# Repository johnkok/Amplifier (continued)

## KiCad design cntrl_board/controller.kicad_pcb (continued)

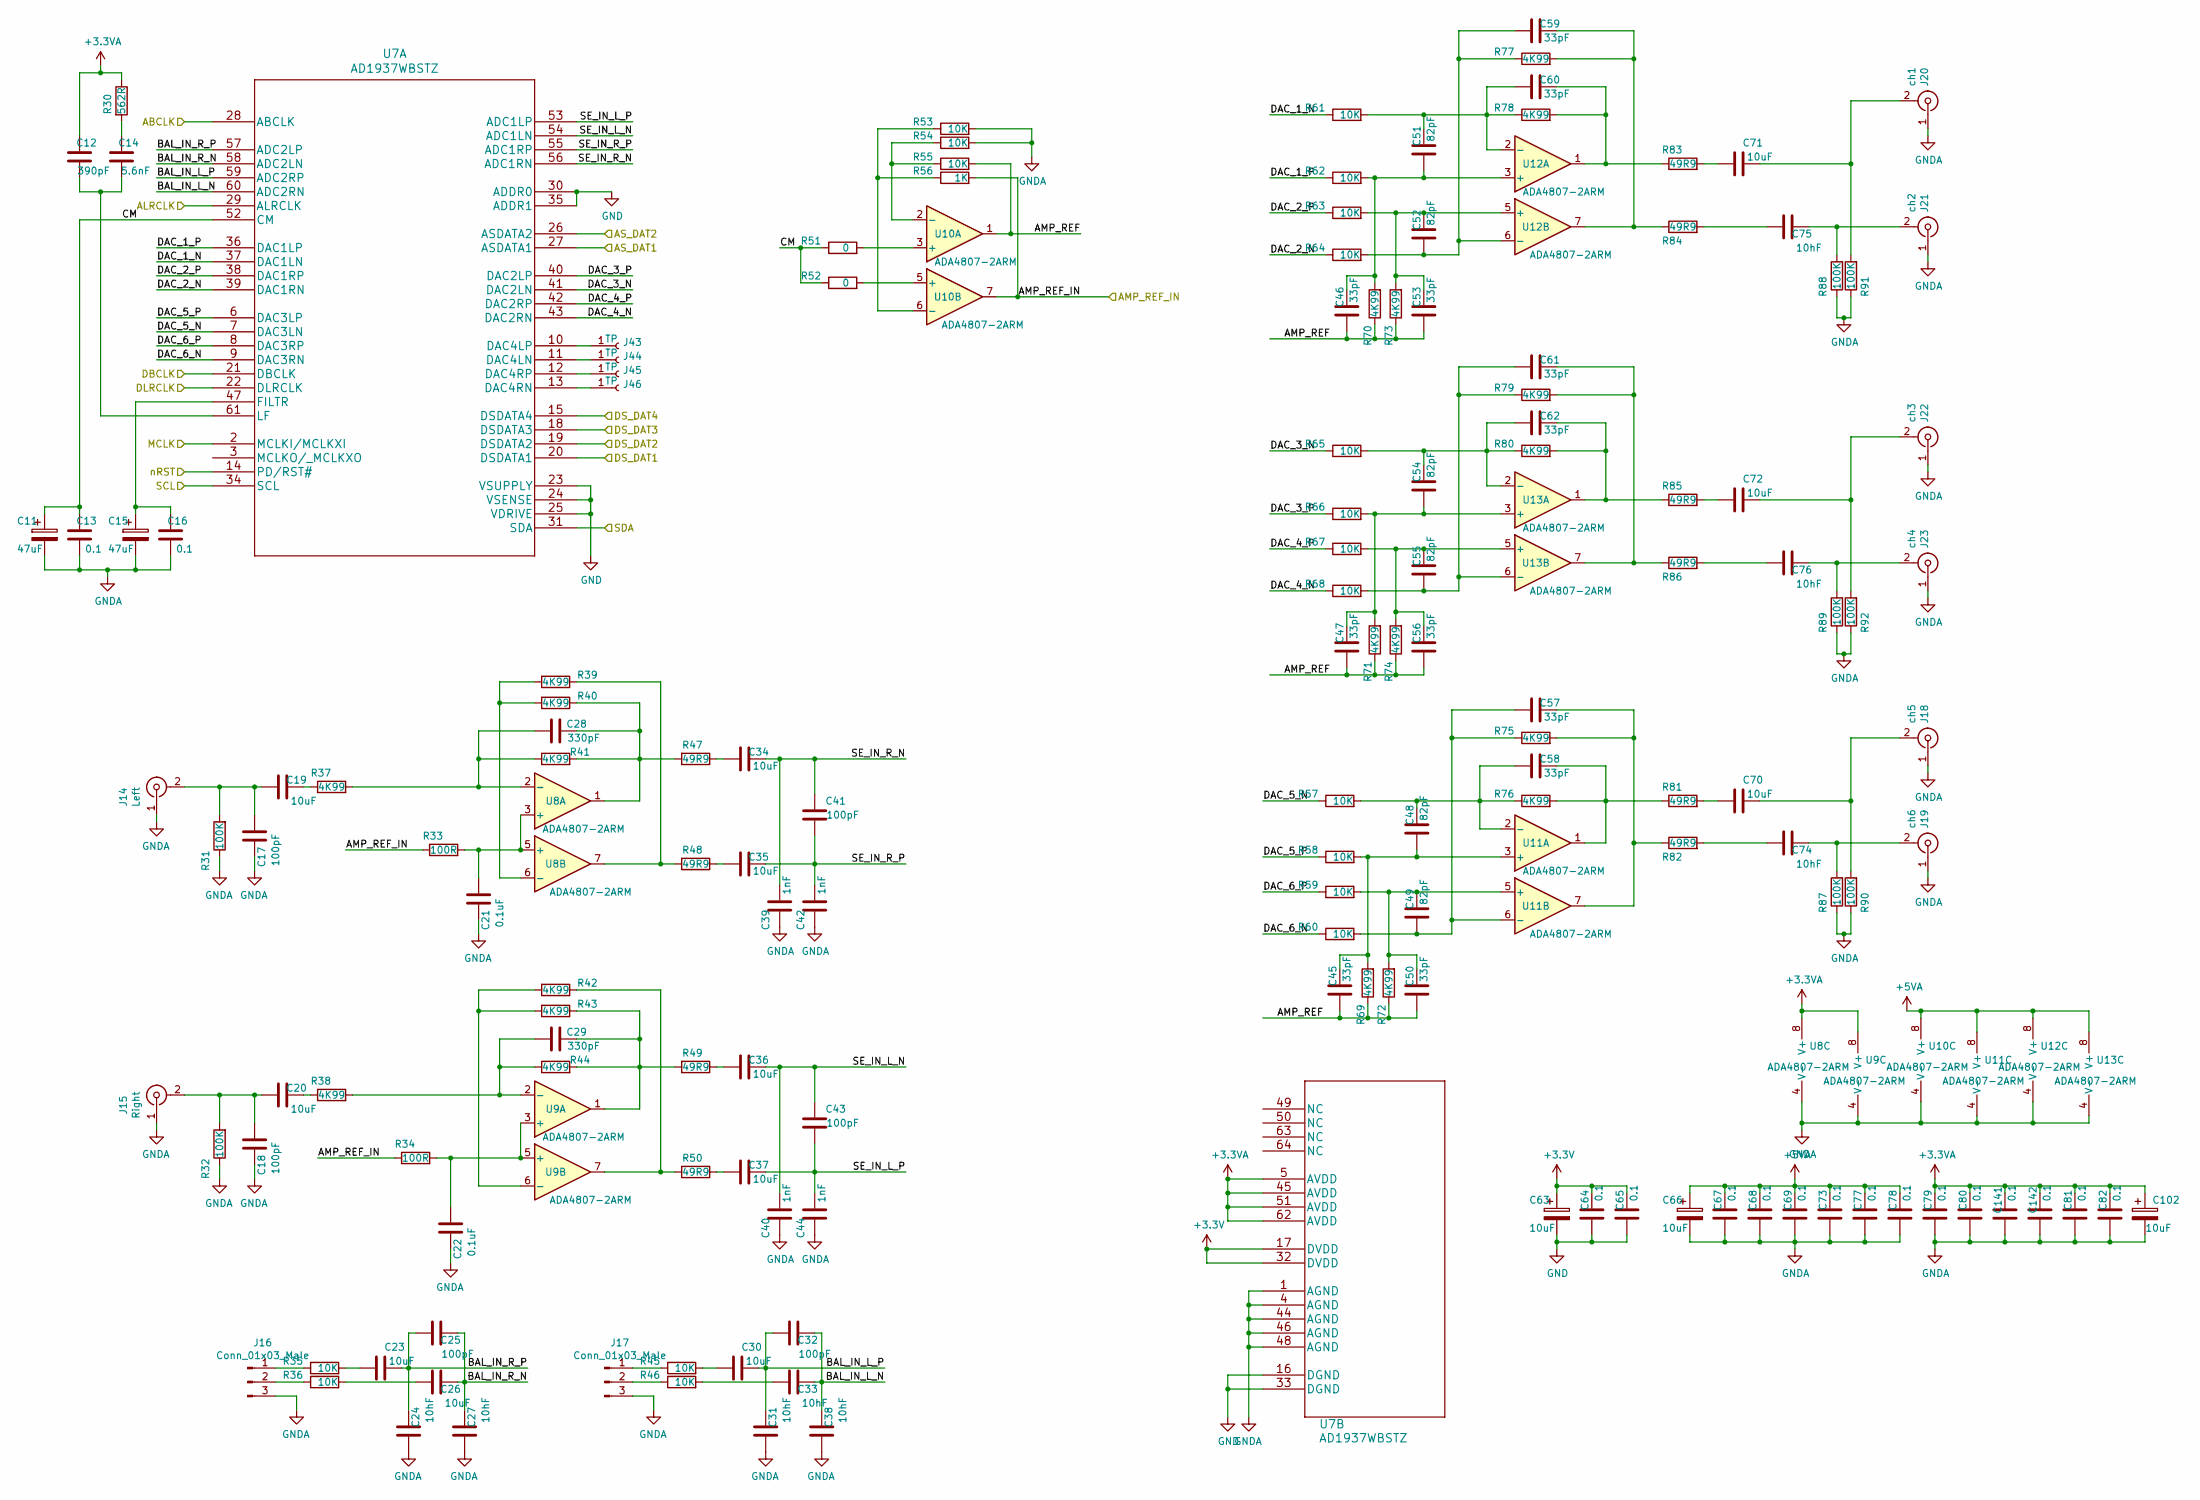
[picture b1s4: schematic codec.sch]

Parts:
C11, C15: 47uF; CP_Elec_6.3x5.3
C12: 390pF; C_0603_1608Metric_Pad1.08x0.95mm_HandSolder
C13, C16, C64, C65, C67, C68, C69, C73, C77, C78, C79, C80, C81, C82, C141, C142: 0.1; C_0603_1608Metric_Pad1.08x0.95mm_HandSolder
C14: 5.6nF; C_0603_1608Metric_Pad1.08x0.95mm_HandSolder
C17, C18, C25, C32, C41, C43: 100pF; C_0603_1608Metric_Pad1.08x0.95mm_HandSolder
C19, C20, C23, C26, C30, C34, C35, C36, C37, C70, C71, C72: 10uF; C_0805_2012Metric_Pad1.18x1.45mm_HandSolder
C21, C22: 0.1uF; C_0603_1608Metric_Pad1.08x0.95mm_HandSolder
C24, C27, C31, C38: 10hF; C_0603_1608Metric_Pad1.08x0.95mm_HandSolder
C28, C29: 330pF; C_0603_1608Metric_Pad1.08x0.95mm_HandSolder
C33, C74, C75, C76: 10hF; C_0805_2012Metric_Pad1.18x1.45mm_HandSolder
C39, C40, C42, C44: 1nF; C_0603_1608Metric_Pad1.08x0.95mm_HandSolder
C45, C46, C47, C50, C53, C56, C57, C58, C59, C60, C61, C62: 33pF; C_0603_1608Metric_Pad1.08x0.95mm_HandSolder
C48, C49, C51, C52, C54, C55: 82pF; C_0603_1608Metric_Pad1.08x0.95mm_HandSolder
C63, C66, C102: 10uF; CP_Elec_5x5.8
J14: Left; RCJ
J15: Right; RCJ
J16, J17: Conn_01x03_Male; PinHeader_1x03_P2.54mm_Vertical
J18: ch5; RCJ
J19: ch6; RCJ
J20: ch1; RCJ
J21: ch2; RCJ
J22: ch3; RCJ
J23: ch4; RCJ
J43, J44, J45, J46: TP; TestPoint_Keystone_5000-5004_Miniature
R30: 562R; R_0603_1608Metric_Pad0.98x0.95mm_HandSolder
R31, R32, R87, R88, R89, R90, R91, R92: 100K; R_0603_1608Metric_Pad0.98x0.95mm_HandSolder
R33, R34: 100R; R_0603_1608Metric_Pad0.98x0.95mm_HandSolder
R35, R36, R45, R46, R53, R54, R55, R57, R58, R59, R60, R61, R62, R63, R64, R65, R66, R67, R68: 10K; R_0603_1608Metric_Pad0.98x0.95mm_HandSolder
R37, R38, R39, R40, R41, R42, R43, R44, R69, R70, R71, R72, R73, R74, R75, R76, R77, R78, R79, R80: 4K99; R_0603_1608Metric_Pad0.98x0.95mm_HandSolder
R47, R48, R49, R50, R81, R82, R83, R84, R85, R86: 49R9; R_0603_1608Metric_Pad0.98x0.95mm_HandSolder
R51, R52: 0; R_0603_1608Metric_Pad0.98x0.95mm_HandSolder
R56: 1K; R_0603_1608Metric_Pad0.98x0.95mm_HandSolder
U7: AD1937WBSTZ
U8, U9, U10, U11, U12, U13: ADA4807-2ARM; MSOP-8_3x3mm_P0.65mm

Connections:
+3.3VA: C12.1, C79.1, C80.1, C81.1, C82.1, C102.1, C141.1, C142.1, R30.1, U7.5 (AVDD), U7.45 (AVDD), U7.51 (AVDD), U7.62 (AVDD), U8.8 (V+), U9.8 (V+); also elsewhere on the board
+5VA: C66.1, C67.1, C68.1, C69.1, C73.1, C77.1, C78.1, U10.8 (V+), U11.8 (V+), U12.8 (V+), U13.8 (V+); also elsewhere on the board
/codec/ABCLK: U7.28 (ABCLK); also elsewhere on the board
/codec/ALRCLK: U7.29 (ALRCLK); also elsewhere on the board
/codec/AMP_REF: C45.2, C46.2, C47.2, C50.2, C53.2, C56.2, R55.2, R69.1, R70.1, R71.1, R72.1, R73.1, R74.1, U10.1
/codec/AMP_REF_IN: R33.1, R34.1, R56.2, U10.7; also elsewhere on the board
/codec/AS_DAT1: U7.27 (ASDATA1); also elsewhere on the board
/codec/AS_DAT2: U7.26 (ASDATA2); also elsewhere on the board
/codec/BAL_IN_L_N: C32.1, C33.1, C38.1, U7.60 (ADC2RN)
/codec/BAL_IN_L_P: C30.1, C31.1, C32.2, U7.59 (ADC2RP)
/codec/BAL_IN_R_N: C25.1, C26.1, C27.1, U7.58 (ADC2LN)
/codec/BAL_IN_R_P: C23.1, C24.1, C25.2, U7.57 (ADC2LP)
/codec/CM: C11.1, C13.1, R51.1, R52.1, U7.52 (CM)
/codec/DAC_1_N: R61.1, U7.37 (DAC1LN)
/codec/DAC_1_P: R62.1, U7.36 (DAC1LP)
/codec/DAC_2_N: R64.1, U7.39 (DAC1RN)
/codec/DAC_2_P: R63.1, U7.38 (DAC1RP)
/codec/DAC_3_N: R65.1, U7.41 (DAC2LN)
/codec/DAC_3_P: R66.1, U7.40 (DAC2LP)
/codec/DAC_4_N: R68.1, U7.43 (DAC2RN)
/codec/DAC_4_P: R67.1, U7.42 (DAC2RP)
/codec/DAC_5_N: R57.1, U7.7 (DAC3LN)
/codec/DAC_5_P: R58.1, U7.6 (DAC3LP)
/codec/DAC_6_N: R60.1, U7.9 (DAC3RN)
/codec/DAC_6_P: R59.1, U7.8 (DAC3RP)
/codec/DBCLK: U7.21 (DBCLK); also elsewhere on the board
/codec/DLRCLK: U7.22 (DLRCLK); also elsewhere on the board
/codec/DS_DAT1: U7.20 (DSDATA1); also elsewhere on the board
/codec/DS_DAT2: U7.19 (DSDATA2); also elsewhere on the board
/codec/DS_DAT3: U7.18 (DSDATA3); also elsewhere on the board
/codec/DS_DAT4: U7.15 (DSDATA4); also elsewhere on the board
/codec/MCLK: U7.2 (MCLKI/MCLKXI); also elsewhere on the board
/codec/SE_IN_L_N: C36.2, C40.2, C43.2, U7.54 (ADC1LN)
/codec/SE_IN_L_P: C37.2, C43.1, C44.2, U7.53 (ADC1LP)
/codec/SE_IN_R_N: C34.2, C39.2, C41.2, U7.56 (ADC1RN)
/codec/SE_IN_R_P: C35.2, C41.1, C42.2, U7.55 (ADC1RP)
/codec/nRST: U7.14 (PD/RST#); also elsewhere on the board
/ucu/CODEC_SCL: U7.34 (SCL); also elsewhere on the board
/ucu/CODEC_SDA: U7.31 (SDA); also elsewhere on the board
GND: C63.2, C64.2, C65.2, U7.16 (DGND), U7.23 (VSUPPLY), U7.24 (VSENSE), U7.25 (VDRIVE), U7.30 (ADDR0), U7.33 (DGND), U7.35 (ADDR1); also elsewhere on the board
GNDA: C11.2, C13.2, C15.2, C16.2, C17.2, C18.2, C21.2, C22.2, C24.2, C27.2, C31.2, C38.2, C39.1, C40.1, C42.1, C44.1, C66.2, C67.2, C68.2, C69.2, C73.2, C77.2, C78.2, C79.2, C80.2, C81.2, C82.2, C102.2, C141.2, C142.2, J14.1 (In), J15.1 (In), J16.3, J17.3, J18.1 (In), J19.1 (In), J20.1 (In), J21.1 (In), J22.1 (In), J23.1 (In), R31.1, R32.1, R53.2, R54.2, R87.1, R88.1, R89.1, R90.1, R91.1, R92.1, U7.1 (AGND), U7.4 (AGND), U7.44 (AGND), U7.46 (AGND), U7.48 (AGND), U8.4 (V-), U9.4 (V-), U10.4 (V-), U11.4 (V-), U12.4 (V-), U13.4 (V-); also elsewhere on the board
unnamed: C12.2, C14.2, U7.61 (LF)
unnamed: C14.1, R30.2
unnamed: C15.1, C16.1, U7.47 (FILTR)
unnamed: C17.1, C19.2, J14.2 (Ext), R31.2
unnamed: C18.1, C20.2, J15.2 (Ext), R32.2
unnamed: C19.1, R37.1
unnamed: C20.1, R38.1
unnamed: C21.1, R33.2, U8.3 (+), U8.5 (+)
unnamed: C22.1, R34.2, U9.3 (+), U9.5 (+)
unnamed: C23.2, R35.2
unnamed: C26.2, R36.2
unnamed: C28.1, R40.1, R41.2, R47.2, U8.1
unnamed: C28.2, R37.2, R41.1, U8.2 (-)
unnamed: C29.1, R43.1, R44.2, R49.2, U9.1
unnamed: C29.2, R38.2, R44.1, U9.2 (-)
unnamed: C30.2, R45.2
unnamed: C33.2, R46.2
unnamed: C34.1, R47.1
unnamed: C35.1, R48.1
unnamed: C36.1, R49.1
unnamed: C37.1, R50.1
unnamed: C45.1, C48.2, R58.2, R69.2, U11.3 (+)
unnamed: C46.1, C51.2, R62.2, R70.2, U12.3 (+)
unnamed: C47.1, C54.2, R66.2, R71.2, U13.3 (+)
unnamed: C48.1, C58.2, R57.2, R76.1, U11.2 (-)
unnamed: C49.1, C50.1, R59.2, R72.2, U11.5 (+)
unnamed: C49.2, C57.2, R60.2, R75.1, U11.6 (-)
unnamed: C51.1, C60.2, R61.2, R78.1, U12.2 (-)
unnamed: C52.1, C53.1, R63.2, R73.2, U12.5 (+)
unnamed: C52.2, C59.2, R64.2, R77.1, U12.6 (-)
unnamed: C54.1, C62.2, R65.2, R80.1, U13.2 (-)
unnamed: C55.1, C56.1, R67.2, R74.2, U13.5 (+)
unnamed: C55.2, C61.2, R68.2, R79.1, U13.6 (-)
unnamed: C57.1, R75.2, R82.1, U11.7
unnamed: C58.1, R76.2, R81.1, U11.1
unnamed: C59.1, R77.2, R84.1, U12.7
unnamed: C60.1, R78.2, R83.1, U12.1
unnamed: C61.1, R79.2, R86.1, U13.7
unnamed: C62.1, R80.2, R85.1, U13.1
unnamed: C70.1, J18.2 (Ext), R90.2
unnamed: C70.2, R81.2
unnamed: C71.1, J20.2 (Ext), R91.2
unnamed: C71.2, R83.2
unnamed: C72.1, J22.2 (Ext), R92.2
unnamed: C72.2, R85.2
unnamed: C74.1, J19.2 (Ext), R87.2
unnamed: C74.2, R82.2
unnamed: C75.1, J21.2 (Ext), R88.2
unnamed: C75.2, R84.2
unnamed: C76.1, J23.2 (Ext), R89.2
unnamed: C76.2, R86.2
unnamed: J16.1, R35.1
unnamed: J16.2, R36.1
unnamed: J17.1, R45.1
unnamed: J17.2, R46.1
unnamed: J43.1, U7.10 (DAC4LP)
unnamed: J44.1, U7.11 (DAC4LN)
unnamed: J45.1, U7.12 (DAC4RP)
unnamed: J46.1, U7.13 (DAC4RN)
unnamed: R39.1, R48.2, U8.7
unnamed: R39.2, R40.2, U8.6 (-)
unnamed: R42.1, R50.2, U9.7
unnamed: R42.2, R43.2, U9.6 (-)
unnamed: R51.2, U10.3 (+)
unnamed: R52.2, U10.5 (+)
unnamed: R53.1, R56.1, U10.6 (-)
unnamed: R54.1, R55.1, U10.2 (-)

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
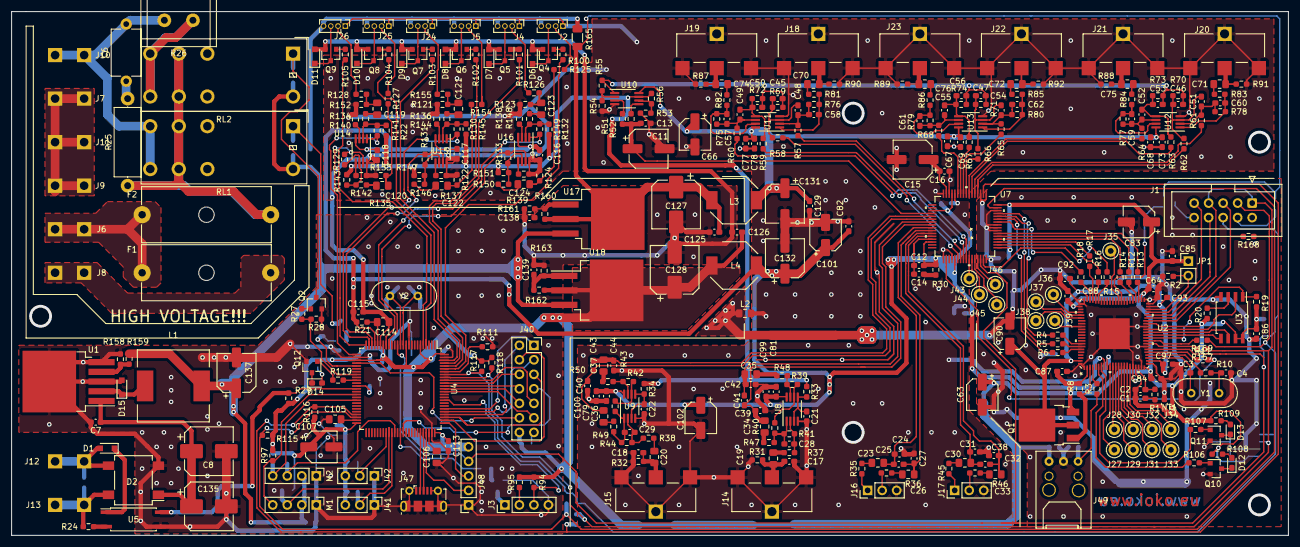
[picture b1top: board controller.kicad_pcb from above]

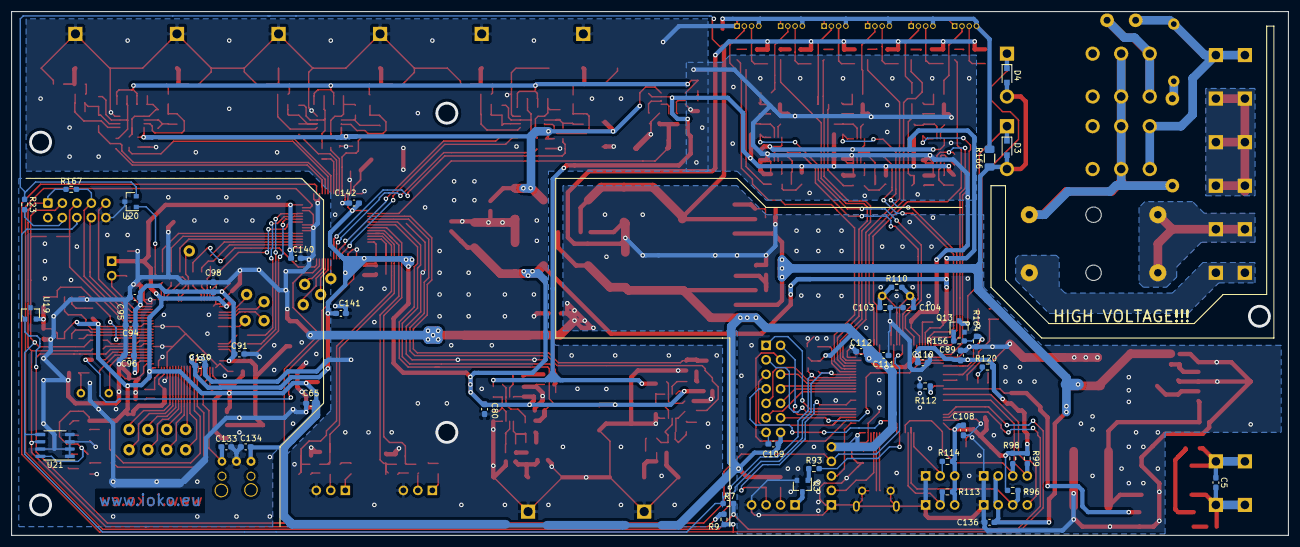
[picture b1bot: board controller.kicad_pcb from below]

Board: 2 copper layers, 223.5 x 91.7 mm, 420 parts (46 on the bottom side), 285 nets.

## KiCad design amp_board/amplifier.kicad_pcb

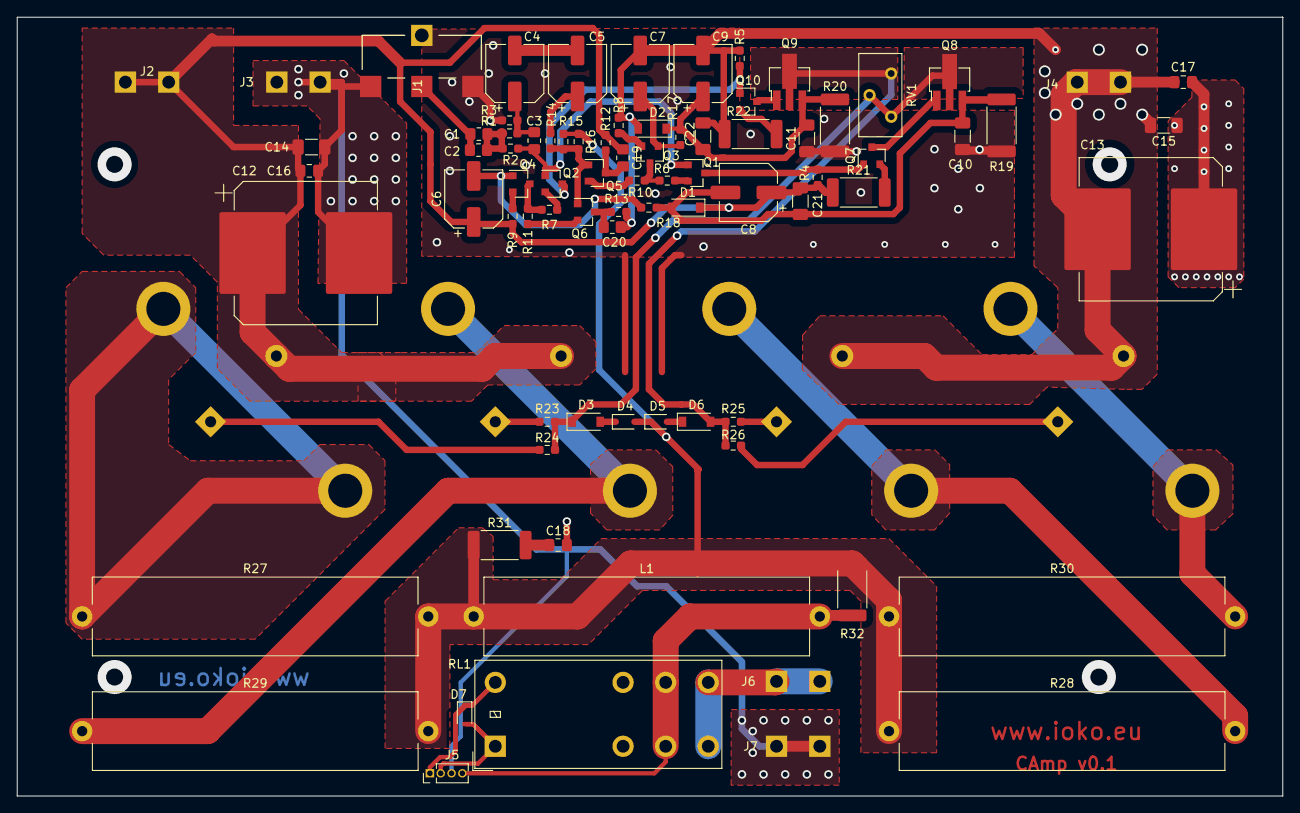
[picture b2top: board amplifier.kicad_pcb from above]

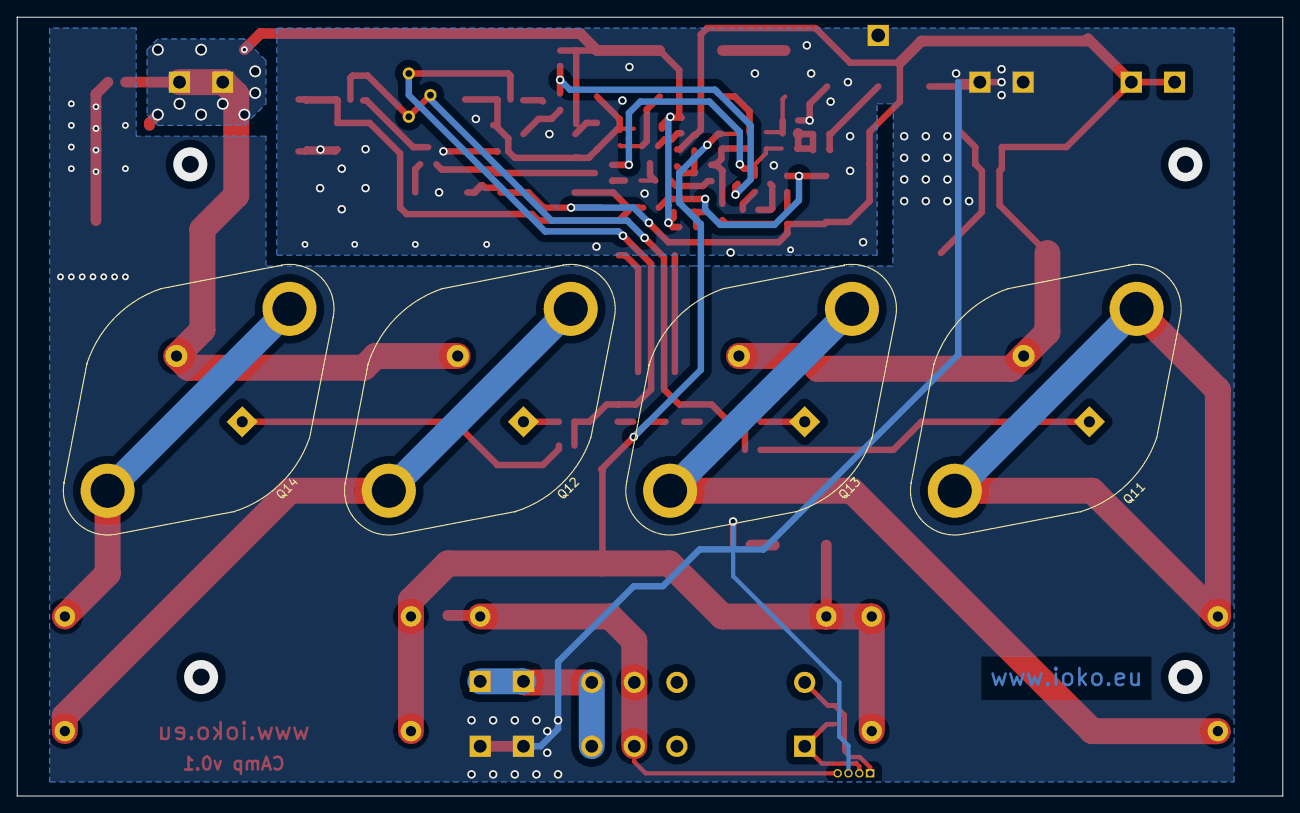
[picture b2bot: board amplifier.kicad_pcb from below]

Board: 2 copper layers, 148.6 x 91.4 mm, 85 parts (4 on the bottom side), 48 nets.

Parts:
C1, C2: 820nF; R_0805_2012Metric_Pad1.20x1.40mm_HandSolder
C3: 220pF; R_0805_2012Metric_Pad1.20x1.40mm_HandSolder
C4, C5, C6, C7, C8, C9: 220uF; CP_Elec_6.3x7.7
C10, C11, C14, C15, C21, C22: 330nF; C_1206_3216Metric_Pad1.33x1.80mm_HandSolder
C12, C13: 100uF/80V; CP_Elec_16x17.5
C16, C17: 10nF; C_0805_2012Metric_Pad1.18x1.45mm_HandSolder
C18: 22nF; C_0805_2012Metric_Pad1.18x1.45mm_HandSolder
C19, C20: 22pF; R_0805_2012Metric_Pad1.20x1.40mm_HandSolder
D1, D2: 3V9; D_SOD-123
D3, D6: 12V; D_SOD-123
D4, D5, D7: 1N4148; D_SOD-323F
J1: AUDIO_IN; RCJ
J2: +VDC; TERMINAL_250
J3: COM; TERMINAL_250
J4: -VDC; TERMINAL_250
J5: OUT_CTL; PinHeader_1x04_P1.27mm_Vertical
J6: SPK_POS; TERMINAL_250
J7: SPK_NEG; TERMINAL_250
L1: 2uH; R_Axial_Power_L38.0mm_W9.0mm_P40.64mm
Q1, Q3, Q5: BC846; SOT-23
Q2, Q4, Q6: BC856; SOT-23
Q7: BC860; SOT-23
Q8: BF621; SOT-89-3_Handsoldering
Q9: BF620; SOT-89-3_Handsoldering
Q10: BC850; SOT-23
Q11, Q13: 2SK135; TO-3
Q12, Q14: 2SJ50; TO-3
R1: 27K; R_0603_1608Metric_Pad0.98x0.95mm_HandSolder
R2: 3K9; R_0603_1608Metric_Pad0.98x0.95mm_HandSolder
R3: 10R; R_0603_1608Metric_Pad0.98x0.95mm_HandSolder
R4, R5, R12, R13: 6K8; R_0603_1608Metric_Pad0.98x0.95mm_HandSolder
R6, R7, R10, R11: 150R; R_0603_1608Metric_Pad0.98x0.95mm_HandSolder
R8, R9: 5K6; R_0603_1608Metric_Pad0.98x0.95mm_HandSolder
R14: 1K; R_0603_1608Metric_Pad0.98x0.95mm_HandSolder
R15: 150K; R_0603_1608Metric_Pad0.98x0.95mm_HandSolder
R16: 39K; R_0603_1608Metric_Pad0.98x0.95mm_HandSolder
R17, R18: 2K2; R_0603_1608Metric_Pad0.98x0.95mm_HandSolder
R19, R20: 10K; R_2512_6332Metric_Pad1.40x3.35mm_HandSolder
R21, R22: 82R; R_2512_6332Metric_Pad1.40x3.35mm_HandSolder
R23, R24, R25, R26: 220R; R_0603_1608Metric_Pad0.98x0.95mm_HandSolder
R27, R28, R29, R30: R22; R_Axial_Power_L38.0mm_W9.0mm_P40.64mm
R31: 10R; R_2512_6332Metric_Pad1.40x3.35mm_HandSolder
R32: 1R; R_2512_6332Metric_Pad1.40x3.35mm_HandSolder
RL1: G2RL-24-DC24; Relay_DPDT_Omron_G2RL
RV1: 220R; Potentiometer_Bourns_3296Y_Vertical

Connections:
+VDC: C6.1, C8.1, C12.1, C14.1, C16.1, C19.1, C21.1, D1.1, J2.1, Q11.2, Q13.2, R4.1, R9.1, R12.1, R21.1
-VDC: C7.2, C9.2, C13.2, C15.2, C17.2, C20.2, C22.2, D2.2, J4.1, Q12.2, Q14.2, R5.2, R8.2, R13.2, R22.2
GND: C10.2, C11.1, C12.2, C13.1, C14.2, C15.1, C16.2, C17.1, C18.2, J1.1, J3.1, J5.3, J7.1, R3.2, R19.2, R20.1
unnamed: C1.1, C2.1, R1.1, R2.2
unnamed: C1.2, C2.2, J1.2
unnamed: C3.1, Q1.1, Q2.1, R2.1
unnamed: C3.2, C4.1, R1.2, R3.1
unnamed: C4.2, C5.2
unnamed: C5.1, R14.2
unnamed: C6.2, Q4.1, R18.2
unnamed: C7.1, Q3.1, R17.2
unnamed: C8.2, C10.1, C21.2, D1.2, Q8.3, R18.1, R19.1
unnamed: C9.1, C11.2, C22.1, D2.1, Q9.3, R17.1, R20.2
unnamed: C18.1, R31.2
unnamed: C19.2, Q5.3, R12.2
unnamed: C20.1, Q6.3, R13.1
unnamed: D3.1, Q8.2, R23.2, R24.2, RV1.1, RV1.2
unnamed: D3.2, D4.1
unnamed: D4.2, D5.1, L1.1, R15.1, R16.1, R27.2, R28.1, R29.2, R30.1, R31.1, R32.2
unnamed: D5.2, D6.1
unnamed: D6.2, Q9.2, R25.2, R26.2, RV1.3
unnamed: D7.1, J5.1, RL1.8
unnamed: D7.2, J5.2, RL1.1
unnamed: J5.4, L1.2, R32.1, RL1.3, RL1.6
unnamed: J6.1, RL1.4, RL1.5
unnamed: Q1.2, R6.2
unnamed: Q1.3, Q7.1, R4.2
unnamed: Q2.2, R7.2
unnamed: Q3.2, R8.1
unnamed: Q3.3, R6.1, R10.2
unnamed: Q4.2, R9.2
unnamed: Q4.3, R7.1, R11.2
unnamed: Q5.1, Q6.1, R14.1, R15.2, R16.2
unnamed: Q5.2, R10.1
unnamed: Q6.2, R11.1
unnamed: Q7.2, R21.2
unnamed: Q7.3, Q8.1
unnamed: Q2.3, Q10.1, R5.1
unnamed: Q10.2, R22.1
unnamed: Q9.1, Q10.3
unnamed: Q11.1, R24.1
unnamed: Q11.3, R27.1
unnamed: Q12.1, R25.1
unnamed: Q12.3, R28.2
unnamed: Q13.1, R23.1
unnamed: Q13.3, R29.1
unnamed: Q14.1, R26.1
unnamed: Q14.3, R30.2

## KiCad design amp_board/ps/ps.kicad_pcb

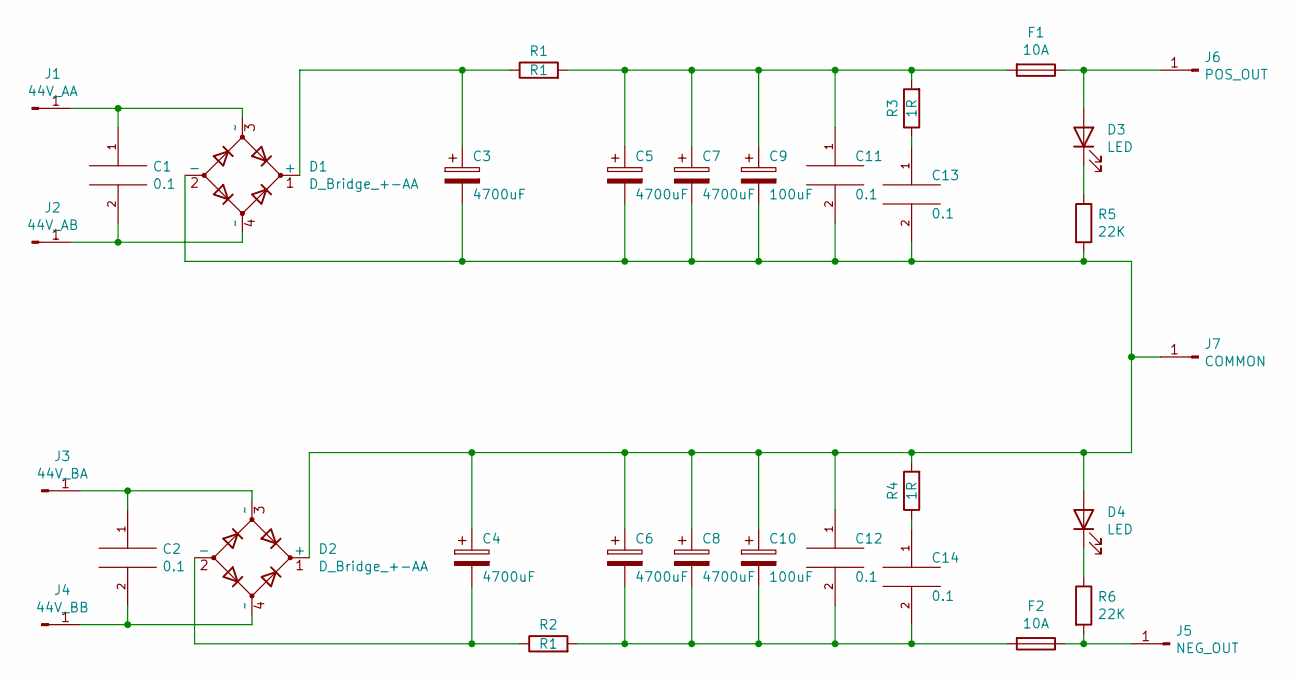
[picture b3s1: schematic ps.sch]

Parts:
C1, C2, C11, C12, C13, C14: 0.1; C_0805_2012Metric_Pad1.18x1.45mm_HandSolder
C3, C4, C5, C6, C7, C8: 4700uF; CP_Radial_D26.0mm_P12.00mm_SnapIn
C9, C10: 100uF; CP_Axial_L10.0mm_D4.5mm_P15.00mm_Horizontal
D1, D2: D_Bridge_+-AA; BRIDGE
D3, D4: LED; LED_0603_1608Metric_Pad1.05x0.95mm_HandSolder
F1, F2: 10A; Fuseholder_Cylinder-5x20mm_Stelvio-Kontek_PTF78_Horizontal_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
J1: 44V_AA; TERMINAL_250
J2: 44V_AB; TERMINAL_250
J3: 44V_BA; TERMINAL_250
J4: 44V_BB; TERMINAL_250
J5: NEG_OUT; TERMINAL_250
J6: POS_OUT; TERMINAL_250
J7: COMMON; TERMINAL_250
R1, R2: R1; R_Axial_Power_L25.0mm_W9.0mm_P30.48mm
R3, R4: 1R; R_2512_6332Metric_Pad1.40x3.35mm_HandSolder
R5, R6: 22K; R_0603_1608Metric_Pad0.98x0.95mm_HandSolder

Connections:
unnamed: C1.1, D1.3 (~~), J1.1
unnamed: C1.2, D1.4 (~~), J2.1
unnamed: C2.1, D2.3 (~~), J3.1
unnamed: C2.2, D2.4 (~~), J4.1
unnamed: C3.1, D1.1 (+), R1.1
unnamed: C4.2, D2.2 (-), R2.1
unnamed: C3.2, C4.1, C5.2, C6.1, C7.2, C8.1, C9.2, C10.1, C11.2, C12.1, C13.2, D1.2 (-), D2.1 (+), D4.2 (A), J7.1, R4.2, R5.2
unnamed: C6.2, C8.2, C10.2, C12.2, C14.2, F2.2, R2.2
unnamed: C5.1, C7.1, C9.1, C11.1, F1.2, R1.2, R3.2
unnamed: C13.1, R3.1
unnamed: C14.1, R4.1
unnamed: D3.1 (K), R5.1
unnamed: D3.2 (A), F1.1, J6.1
unnamed: D4.1 (K), R6.1
unnamed: F2.1, J5.1, R6.2

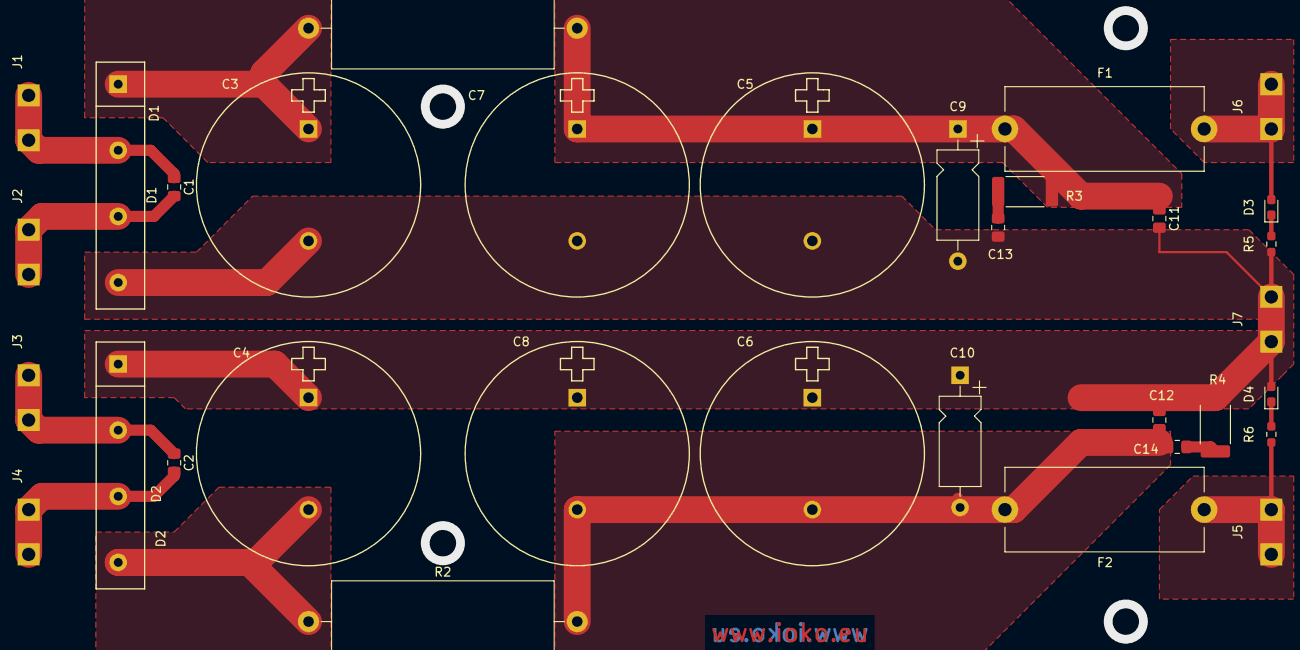
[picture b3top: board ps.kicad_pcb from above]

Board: 2 copper layers, 33 parts (0 on the bottom side), 15 nets.

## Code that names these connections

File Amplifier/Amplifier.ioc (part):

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PD12.GPIO_Label=FAN1_IN
PC7.GPIOParameters=GPIO_Label
PH0-OSC_IN.Signal=RCC_OSC_IN
PC10.GPIO_PuPd=GPIO_PULLUP
PE11.GPIOParameters=GPIO_Label
PB10.Mode=I2C
PC12.Signal=SPI3_MOSI
PD3.GPIOParameters=GPIO_PuPd,GPIO_Label
PC6.GPIO_Label=BUT_LED
PB6.GPIO_Label=DSP_SCL
PD6.GPIO_Label=LCD_RST
PB3.GPIO_Speed=GPIO_SPEED_FREQ_VERY_HIGH
PE6.GPIO_Label=CH6_OUT
RCC.SYSCLKSource=RCC_SYSCLKSOURCE_PLLCLK
PD7.GPIO_PuPd=GPIO_PULLUP
PE2.Mode=Trace_Synchro_2bits_SW
PB6.Signal=I2C1_SCL
PC7.Signal=S_TIM3_CH2
PB6.Mode=I2C
PC3.Signal=ADCx_IN13
PD0.Signal=GPIO_Input
PE5.Signal=GPIO_Output
PE1.Signal=GPIO_Output
PB3.Mode=Full_Duplex_Master
PB0.GPIOParameters=GPIO_Label
PE0.GPIOParameters=GPIO_Label
PE9.Signal=S_TIM1_CH1
PA5.GPIO_PuPd=GPIO_PULLDOWN
PE2.Signal=SYS_TRACECLK
Mcu.Package=LQFP100
PB9.Signal=GPIO_Output
PD12.Signal=S_TIM4_CH1
PA5.GPIOParameters=GPIO_PuPd,GPIO_Label
PC11.Mode=Full_Duplex_Master
PB5.GPIO_Speed=GPIO_SPEED_FREQ_VERY_HIGH
PB10.GPIOParameters=GPIO_Label
PC12.GPIO_PuPd=GPIO_PULLUP
PD3.GPIO_PuPd=GPIO_PULLUP
PB5.GPIO_Mode=GPIO_MODE_AF_PP
PD6.GPIOParameters=PinState,GPIO_PuPd,GPIO_Label
PA15.GPIOParameters=GPIO_PuPd,GPIO_Label
PD3.Signal=GPIO_Input
PC6.Signal=S_TIM3_CH1
PC2.Signal=ADCx_IN12
PB11.GPIO_Label=CODEC_SDA
PD13.GPIOParameters=GPIO_Label
PD7.Signal=GPIO_Output
PC11.GPIOParameters=GPIO_PuPd,GPIO_Label
PC3.GPIOParameters=GPIO_Label
PB8.GPIO_Label=CH1_OUT
PB11.Mode=I2C
PB11.GPIOParameters=GPIO_Label
PB4.GPIO_PuPd=GPIO_PULLUP
PE9.GPIO_Label=FAN1_CTRL
PB10.Signal=I2C2_SCL
PA5.Signal=GPIO_Output
PD7.PinState=GPIO_PIN_SET
PC12.Mode=Full_Duplex_Master
PE1.GPIO_Label=CH4_OUT
PC2.GPIOParameters=GPIO_Label
PC10.GPIOParameters=GPIO_PuPd,GPIO_Label
PB3.GPIO_Mode=GPIO_MODE_AF_PP
PA13.Mode=Trace_Synchro_2bits_SW
PC7.GPIO_Label=LCD_BL
PD14.GPIOParameters=GPIO_Label
PA4.Signal=GPIO_Output
PB5.Signal=SPI1_MOSI
PA5.GPIO_Label=AC_CTRL
PD11.Signal=GPIO_Input
PB5.GPIO_PuPd=GPIO_PULLUP
PE5.GPIO_Label=CH5_OUT
PC12.GPIO_Label=TOUCH_MOSI
PD0.GPIO_PuPd=GPIO_PULLUP
PD0.GPIOParameters=GPIO_PuPd,GPIO_Label
PE3.Signal=SYS_TRACED0
PC3.GPIO_Label=CH6
PB0.Signal=GPIO_Output
PD7.GPIOParameters=GPIO_Speed,PinState,GPIO_PuPd,GPIO_Label,GPIO_ModeDefaultOutputPP
Mcu.UserName=STM32F407VETx
PE11.GPIO_Label=FAN2_CTRL
PC10.Signal=SPI3_SCK
PD0.GPIO_Label=TOUCH_IRQ
PB0.GPIO_Label=LED
PB11.Signal=I2C2_SDA
PE5.GPIOParameters=GPIO_Label
PB5.GPIOParameters=GPIO_Speed,GPIO_PuPd,GPIO_Mode
PD13.Signal=GPIO_Input
PA15.GPIO_Label=TOUCH_nCS
PC11.GPIO_PuPd=GPIO_PULLUP
PB4.GPIOParameters=GPIO_Speed,GPIO_PuPd,GPIO_Mode
PB4.GPIO_Mode=GPIO_MODE_AF_PP
PD11.GPIO_Label=TS2
PH0-OSC_IN.Mode=HSE-External-Oscillator
RCC.HSE_VALUE=12000000
PA4.GPIO_PuPd=GPIO_PULLUP
PA15.Mode=NSS_Signal_Hard_Output
PA4.GPIO_Speed=GPIO_SPEED_FREQ_VERY_HIGH
PD7.GPIO_Speed=GPIO_SPEED_FREQ_VERY_HIGH
PB3.GPIO_PuPd=GPIO_PULLUP
PB4.Mode=Full_Duplex_Master
PA14.Mode=Trace_Synchro_2bits_SW
PB5.Mode=Full_Duplex_Master
PC11.GPIO_Label=TOUCH_MISO
PD6.PinState=GPIO_PIN_SET
PB3.GPIOParameters=GPIO_Speed,GPIO_PuPd,GPIO_Mode
PB7.Signal=I2C1_SDA
PE4.Mode=Trace_Synchro_2bits_SW
PE4.Signal=SYS_TRACED1
PE6.GPIOParameters=GPIO_Label
PB6.GPIOParameters=GPIO_Label
PD7.GPIO_Label=LCD_DC
PB7.GPIO_Label=DSP_SDA
PH1-OSC_OUT.Mode=HSE-External-Oscillator
PD13.GPIO_Label=TS1
PA15.Signal=SPI3_NSS
PA4.GPIO_ModeDefaultOutputPP=GPIO_MODE_OUTPUT_PP
PE0.GPIO_Label=CH3_OUT
PD3.GPIO_Label=PON
PE7.Signal=GPIO_Input
PD6.Signal=GPIO_Output
PC2.GPIO_Label=CH5
PE3.Mode=Trace_Synchro_2bits_SW
PB4.Signal=SPI1_MISO
PB8.GPIOParameters=GPIO_Label
PB9.GPIO_Label=CH2_OUT
PC10.GPIO_Label=TOUCH_SCK
PC11.Signal=SPI3_MISO
PC10.Mode=Full_Duplex_Master
PE9.GPIOParameters=GPIO_Label
PB9.GPIOParameters=GPIO_Label
PC12.GPIOParameters=GPIO_PuPd,GPIO_Label
PA13.Signal=SYS_JTMS-SWDIO
PA4.PinState=GPIO_PIN_SET
PD12.GPIOParameters=GPIO_Label
PB10.GPIO_Label=CODEC_SCL
PE7.GPIOParameters=GPIO_Label
PB7.GPIOParameters=GPIO_Label
PE11.Signal=S_TIM1_CH2
board=custom
PD11.GPIOParameters=GPIO_Label
PB4.GPIO_Speed=GPIO_SPEED_FREQ_VERY_HIGH
PH1-OSC_OUT.Signal=RCC_OSC_OUT
PD14.GPIO_Label=FAN2_IN
PA4.GPIOParameters=GPIO_Speed,PinState,GPIO_PuPd,GPIO_ModeDefaultOutputPP
PE6.Signal=GPIO_Output
Mcu.Name=STM32F407V(E-G)Tx
PE0.Signal=GPIO_Input
PE7.GPIO_Label=AC_IN
PD14.Signal=S_TIM4_CH3
PB3.Signal=SPI1_SCK
RCC.SYSCLKFreq_VALUE=168000000
PB7.Mode=I2C
PA14.Signal=SYS_JTCK-SWCLK
PC6.GPIOParameters=GPIO_Label
PA15.GPIO_PuPd=GPIO_PULLUP
PB8.Signal=GPIO_Output
PD7.GPIO_ModeDefaultOutputPP=GPIO_MODE_OUTPUT_PP
PE1.GPIOParameters=GPIO_Label
PD6.GPIO_PuPd=GPIO_PULLUP

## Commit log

2021-07-05 update components
2021-09-18 Fix misc issues
2021-09-19 fw added
2021-10-19 update xformer soft startup
2021-10-19 add DSP project
2021-10-19 update crossover
2021-10-22 add 3d print models
2021-10-22 update fw file structure
2021-10-23 update gui
2021-11-05 clean directory
2021-11-07 fix CPU-DSP channel
